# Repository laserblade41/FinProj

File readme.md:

<h1 align="center">FinWatch</h1>

<p align="center">
  An open-source, Zephyr-powered BLE smartwatch with a modular I²C expansion port.<br>
  Final project in Computer Engineering, Bar-Ilan University (Project 323).
</p>

## About

FinWatch is a complete custom smartwatch: the PCB (KiCad), the firmware (Zephyr RTOS / nRF Connect SDK) and a documented protocol for attaching new hardware to it.

Most smartwatches, commercial and open-source, are sealed. The sensors are fixed at manufacture, so a new measurement means a new watch. FinWatch asks whether a finished watch can be extended instead. A four-pin pogo connector on the back of the case carries 3.3 V, GND and an I²C bus. A module clipped onto it describes itself to the watch at runtime, and the firmware does not need to know about that module in advance.

The protocol that makes this work is the **FinWatch Module Protocol (FWMP)**. It is a self-describing, CRC-protected descriptor format. The host treats every byte from a module as untrusted and validates it before use.

The full write-up (design, protocol specification, verification, lessons learned) is in [report/main.pdf](report/main.pdf).

## Features

### Hardware

- **Nordic nRF5340** dual-core SoC (Cortex-M33 application core plus a separate network core running the BLE controller)
- **Nordic nPM1300** PMIC: Li-Po charging, fuel gauge, regulated 1.8 V and 3.3 V rails
- **GC9A01** 240×240 round LCD (SPI) with **CST816S** capacitive touch (I²C)
- **Bosch BMI270** 6-axis IMU with an any-motion interrupt, so the MCU sleeps until the wrist moves
- **Macronix MX25U51245G** 512 Mbit SPI NOR flash for assets and settings
- 32.768 kHz crystal for the RTC
- Two user buttons
- **4-pin pogo expansion port** (3.3 V, GND, SDA, SCL), level-shifted from the SoC's 1.8 V domain by a PCA9306
- 4-layer, 46 mm round PCB designed in KiCad (see [kicad/](kicad/))

### Software

- Zephyr RTOS on the nRF Connect SDK (NCS v3.2.1), with the application running in TF-M non-secure
- LVGL user interface: watch face showing time, date, battery and steps, plus a screen for the attached module
- Interrupt-driven step counting. The IMU wakes the host and the host only samples while the wrist is moving
- BLE with battery level notifications
- LittleFS on the external flash for persistent settings
- **FWMP host**: hot-plug detection, descriptor validation, input and output reports, adaptive polling, and I²C bus recovery
- Expansion runs at the lowest thread priority, so a misbehaving module cannot stall the display, sensors or radio link
- Hardware is described in the Devicetree only, so the same firmware runs on the nRF5340-DK and the custom PCB

## Expansion port and FWMP

FWMP is specified in three layers:

| Layer | What it defines |
| --- | --- |
| Electrical | Four contacts, 3.3 V supply, no pull-ups on the module side, level shifting on the watch |
| Logical | Register map and a TLV descriptor (identity, capabilities, report sizes, preferred poll rate) protected by a CRC-16 |
| Behavioural | Presence detection, enumeration, polling state machine, and recovery from faults |

The host rejects bad magic, bad protocol version, bad CRC, oversized lengths and TLV overruns. It also recovers a jammed bus. All of these paths were exercised with injected faults against a mock module. See section 4 of the report for the full specification and for how to write a compliant module.

## Hardware

| Path | Contents |
| --- | --- |
| [kicad/](kicad/) | Schematic, PCB layout, custom symbols, footprints and 3D models |
| [kicad/watch_thing_alt.pdf](kicad/watch_thing_alt.pdf) | Schematic PDF |
| [kicad/components/board1_nrf5340/](kicad/components/board1_nrf5340/) | Gerber and drill files |

**Revision status**

- **Revision A** was manufactured and assembled. The power rails came up correctly, but `SWDIO` and `SWDCLK` were never routed, so the board could not be programmed.
- **Revision B** exposes SWD on test pads: `SWDIO` on TP4, `SWDCLK` on TP3, `nRESET` on TP2. The lesson from this defect became a pre-fabrication checklist, documented in the report.

## Firmware

Above: the firmware running on the nRF5340-DK with the round display wired up.

```
code/
├── prj.conf                  Kconfig
├── boards/                   Devicetree overlays
├── child_image/hci_ipc.conf  Network-core BLE controller config
└── src/
    ├── main.c
    ├── ble/        BLE and battery notifications
    ├── buttons/    short and long press handling
    ├── display/    LVGL, watch face, module screen
    ├── expansion/  FWMP host, transport and mock module
    ├── pmic/       nPM1300: charger and fuel gauge
    ├── rtc/        timekeeping on the 32.768 kHz crystal
    ├── sensor/     BMI270 any-motion and step counting
    ├── storage/    external flash and LittleFS
    └── touch/      CST816S
```

### Building
```
IMPORTANT: the board itself does not include a bootloader to flash the firmware, in our case we used the one in the nRF5340DK.
```
1. Install the [nRF Connect SDK](https://docs.nordicsemi.com/bundle/ncs-latest/page/nrf/installation.html) **v3.2.1** and open an NCS shell.
2. Build and flash:

```sh
cd code
west build -b nrf5340dk/nrf5340/cpuapp/ns
west flash
```

To test the expansion protocol without any module hardware, enable the mock backend, which simulates a "Test Dial" module:

```sh
west build -b nrf5340dk/nrf5340/cpuapp/ns -- -DCONFIG_FINWATCH_EXPANSION_MOCK=y
```

> For the custom PCB, rename [code/boards/your_board.overlay](code/boards/your_board.overlay) to match your board target and confirm every pin marked `/* [PCB] */` against the schematic before flashing.

## Verification

- Firmware verified on the nRF5340-DK: display, touch, IMU, buttons and BLE
- FWMP verified against a mock module, including hot-plug and six injected-fault classes
- Revision A power rails verified; Revision B bring-up: *TODO*

Full results and their limits are in the report.

## Repository layout

| Folder | Contents |
| --- | --- |
| [code/](code/) | Zephyr firmware |
| [kicad/](kicad/) | PCB design files |
| [report/](report/) | Final project report (LaTeX and PDF) and presentation |
| [pics/](pics/) | Photos and renders |

## Authors

- **Omer Lazaros**
- **Chen Leibov**

Supervised by Prof. Leonid Yavitz. Project mentor: David Freud. Faculty of Engineering, Bar-Ilan University.

## Thanks

Thanks to the Zephyr Project, Nordic Semiconductor (nRF Connect SDK and its courses) and KiCad, whose open tools and documentation made this possible. [ZSWatch](https://github.com/ZSWatch/ZSWatch) was a major inspiration for this project.

## License

*TODO: pick a license (for example GPL-3.0 or MIT for the firmware and CERN-OHL for the hardware) and add a LICENSE file.*

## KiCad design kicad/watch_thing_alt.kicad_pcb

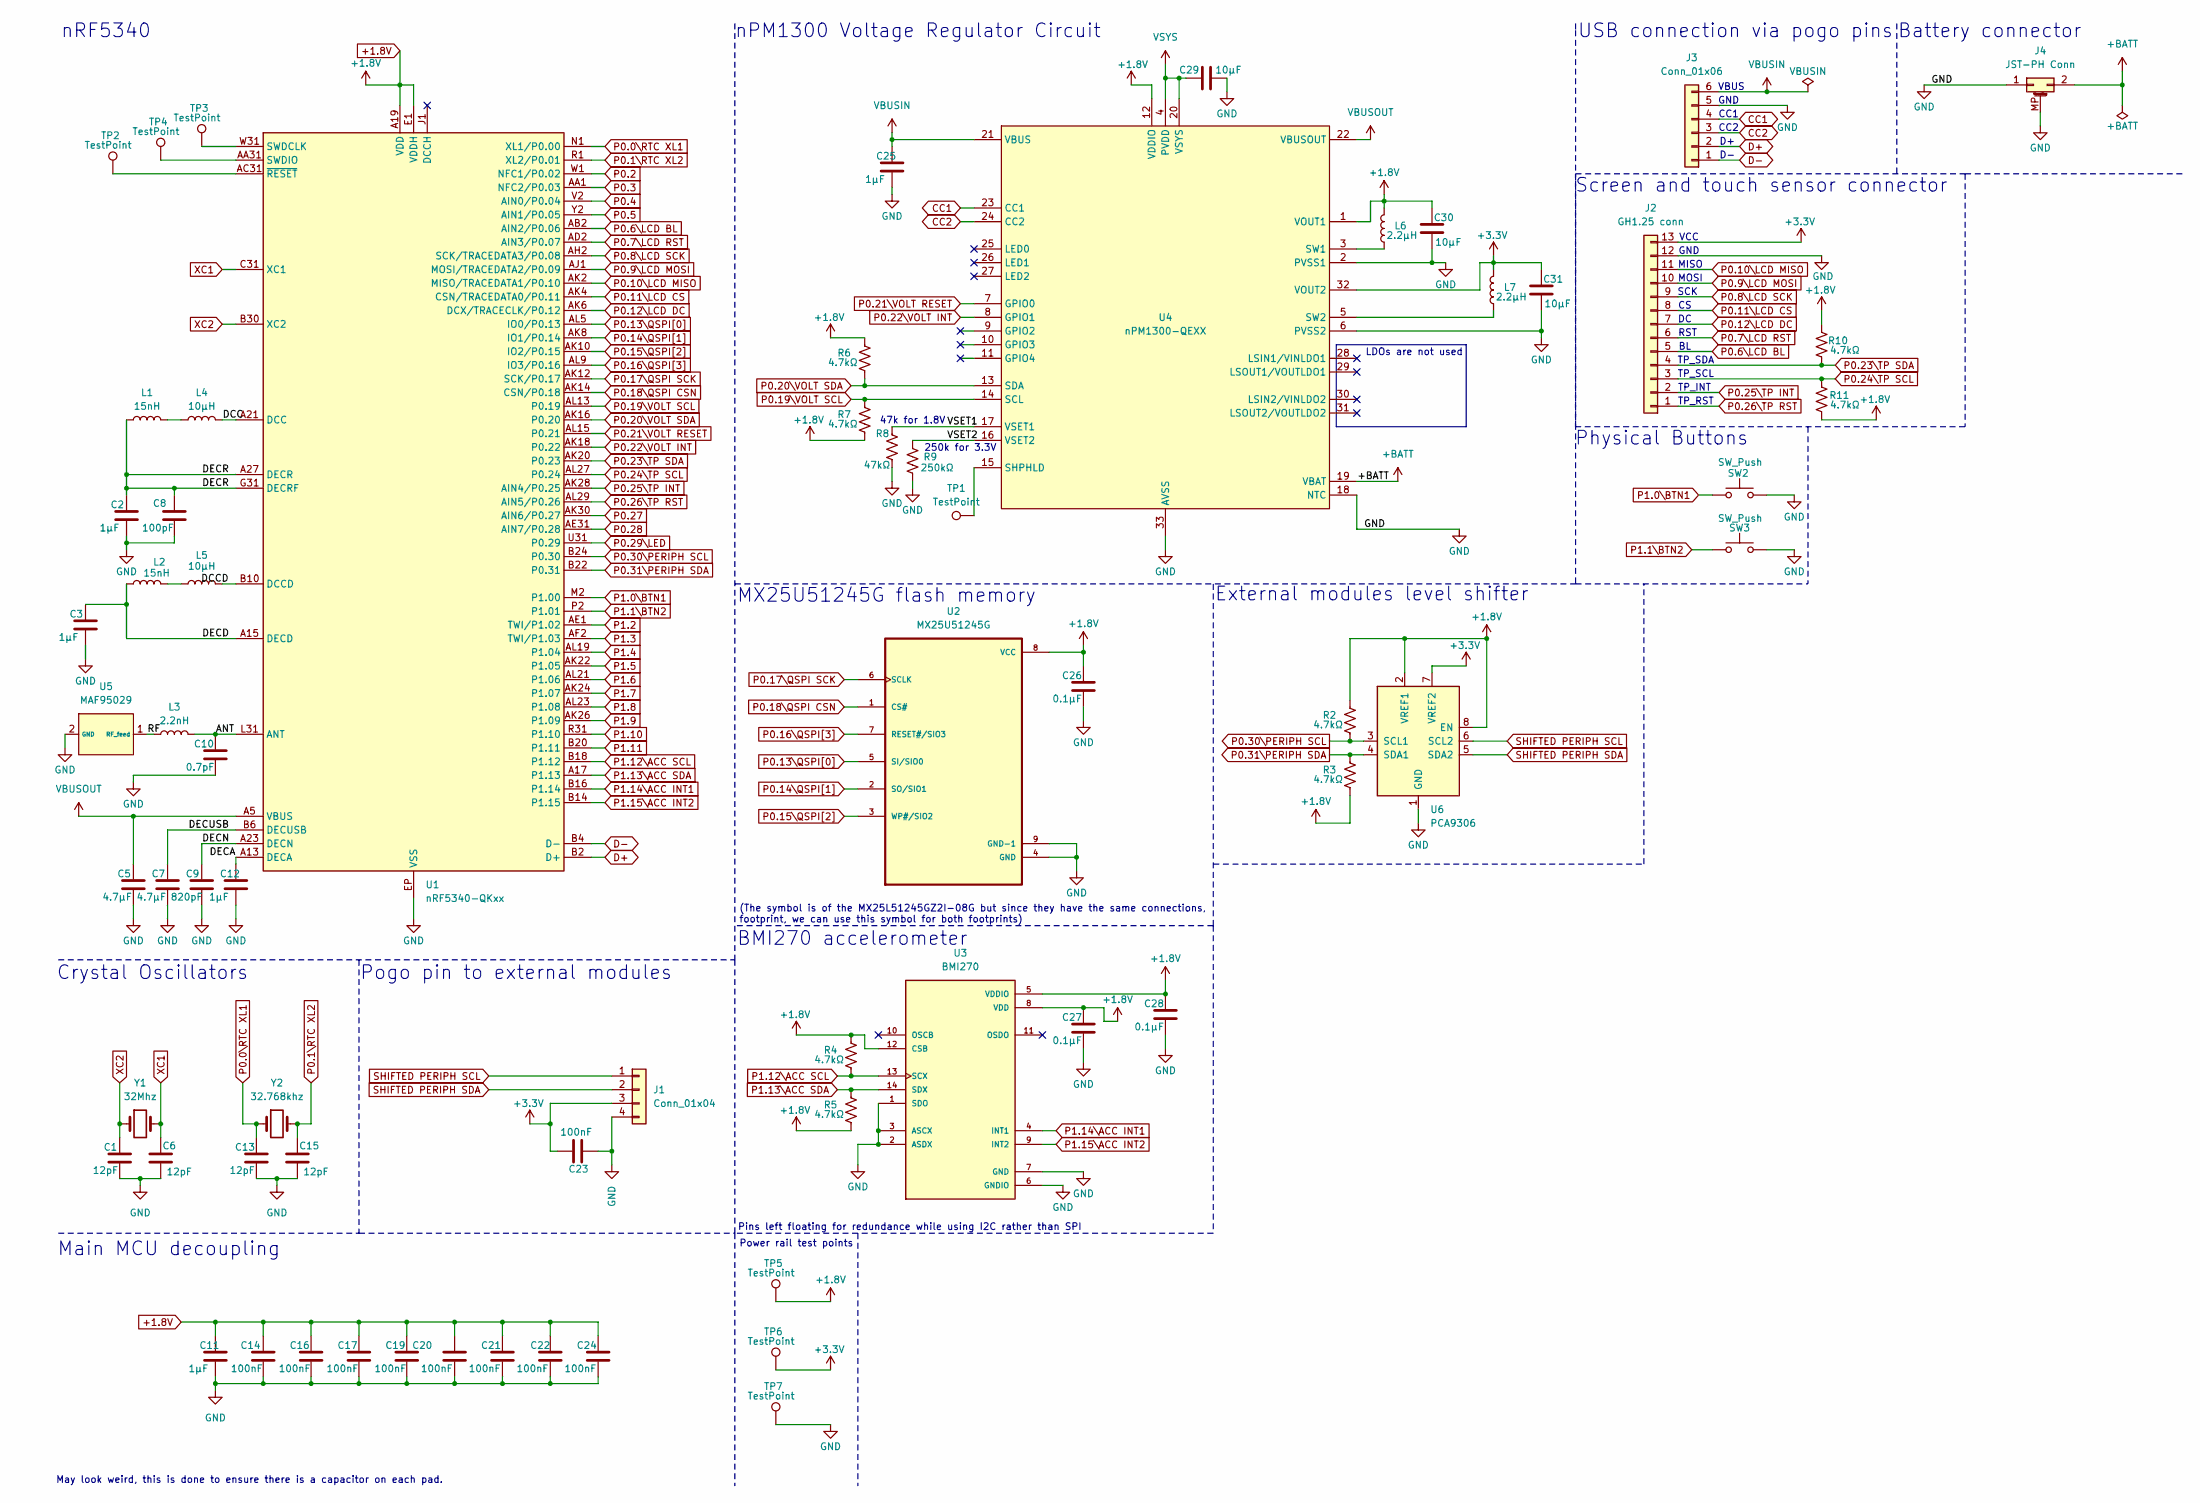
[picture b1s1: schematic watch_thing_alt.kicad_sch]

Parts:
C1, C6, C13, C15: 12pF; C_0402_1005Metric
C2, C3, C11, C12, C25: 1μF; C_0402_1005Metric
C5, C7: 4.7μF; C_0402_1005Metric
C8: 100pF; C_0402_1005Metric
C9: 820pF; C_0402_1005Metric
C10: 0.7pF; C_0402_1005Metric
C14, C16, C17, C19, C20, C21, C22, C23, C24: 100nF; C_0402_1005Metric
C26, C27, C28: 0.1μF; C_0402_1005Metric
C29, C30, C31: 10μF; C_0402_1005Metric
J1: Conn_01x04; 4_Pin_PogoPin
J2: GH1.25 conn; Molex_PicoBlade_53048-1310_1x13_P1.25mm_Horizontal
J3: Conn_01x06; 6_Pin_PogoPin
J4: JST-PH Conn; JST_SH_SM02B-SRSS-TB_1x02-1MP_P1.00mm_Horizontal
L1, L2: 15nH; L_0402_1005Metric
L3: 2.2nH; L_0402_1005Metric
L4, L5: 10μH; L_0402_1005Metric
L6, L7: 2.2μH; L_0402_1005Metric
R2, R3, R4, R5, R6, R7, R10, R11: 4.7kΩ; R_0402_1005Metric
R8: 47kΩ; R_0402_1005Metric
R9: 250kΩ; R_0402_1005Metric
SW2, SW3: SW_Push; SW_Push_1P1T-MP_NO_Horizontal_Alps_SKRTLAE010
TP1, TP2, TP3, TP4, TP5, TP6, TP7: TestPoint; TestPoint_Pad_1.0x1.0mm
U1: nRF5340-QKxx; Nordic_AQFN-94-1EP_7x7mm_P0.4mm
U2: MX25U51245G; SON127P600X800X80-9N
U3: BMI270; XDCR_BMI270
U4: nPM1300-QEXX; QFN-32-1EP_5x5mm_P0.5mm_EP3.6x3.6mm_ThermalVias
U5: MAF95029; MAF92029
U6: PCA9306; SOP50P310X90-8N
Y1: 32Mhz; Crystal_SMD_3225-4Pin_3.2x2.5mm_HandSoldering
Y2: 32.768khz; XTAL_ABS06-32.768KHZ-T

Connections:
+1.8V: C11.1, C14.1, C16.1, C17.1, C19.1, C20.1, C21.1, C22.1, C24.1, C26.1, C27.1, C28.1, C30.1, L6.2, R2.1, R3.2, R4.1, R5.2, R6.1, R7.2, R10.1, R11.2, TP5.1 (1_1), U1.A19 (VDD), U1.AC1 (VDD), U1.AG1 (VDD), U1.AJ31 (VDD), U1.AL3 (VDD), U1.AL7 (VDD), U1.AL11 (VDD), U1.AL17 (VDD), U1.AL25 (VDD), U1.B8 (VDD), U1.B28 (VDD), U1.C1 (VDD), U1.E1 (VDDH), U1.E31 (VDD), U1.L1 (VDD), U1.N31 (VDD), U1.U1 (VDD), U2.8 (VCC), U3.5 (VDDIO), U3.8 (VDD), U3.12 (CSB), U4.1 (VOUT1), U4.12 (VDDIO), U6.2 (VREF1), U6.8 (EN)
+3.3V: C23.2, C31.1, J1.3, J2.13, L7.2, TP6.1 (1_1), U4.32 (VOUT2), U6.7 (VREF2)
+BATT: J4.2, U4.19 (VBAT)
/ANT: C10.1, L3.2, U1.L31 (ANT)
/DCC: L4.2, U1.A21 (DCC)
/DCCD: L5.2, U1.B10 (DCCD)
/DECA: C12.1, U1.A13 (DECA)
/DECD: C3.1, L2.1, U1.A15 (DECD)
/DECN: C9.1, U1.A23 (DECN)
/DECR: C2.1, C8.1, L1.1, U1.A27 (DECR), U1.G31 (DECRF)
/DECUSB: C7.1, U1.B6 (DECUSB)
/RF: L3.1, U5.1 (RF_feed)
/VSET1: R8.2, U4.17 (VSET1)
/VSET2: R9.1, U4.16 (VSET2)
CC1: J3.4, U4.23 (CC1)
CC2: J3.3, U4.24 (CC2)
D+: J3.2, U1.B2 (D+)
D-: J3.1, U1.B4 (D-)
GND: C1.2, C2.2, C3.2, C5.2, C6.2, C7.2, C8.2, C9.2, C10.2, C11.2, C12.2, C13.2, C14.2, C15.2, C16.2, C17.2, C19.2, C20.2, C21.2, C22.2, C23.1, C24.2, C25.2, C26.2, C27.2, C28.2, C29.2, C30.2, C31.2, J1.4, J2.12, J3.5, J4.1, J4.MP (MountPin), R8.1, R9.2, SW2.2, SW3.2, TP7.1 (1_1), U1.EP (VSS), U2.4 (GND), U2.9 (GND-1), U3.1 (SDO), U3.2 (ASDX), U3.3 (ASCX), U3.6 (GNDIO), U3.7 (GND), U4.2 (PVSS1), U4.6 (PVSS2), U4.18 (NTC), U4.33 (AVSS), U5.2 (GND), U6.1 (GND)
unnamed: L1.2, L4.1
unnamed: L2.2, L5.1
unnamed: TP3.1 (1_1), U1.W31 (SWDCLK)
unnamed: TP4.1 (1_1), U1.AA31 (SWDIO)
unnamed: TP2.1 (1_1), U1.AC31 (~RESET)
unnamed: TP1.1 (1_1), U4.15 (SHPHLD)
unnamed: L6.1, U4.3 (SW1)
unnamed: L7.1, U4.5 (SW2)
P0.0\RTC XL1: C13.1, U1.N1 (XL1/P0.00), Y2.1
P0.1\RTC XL2: C15.1, U1.R1 (XL2/P0.01), Y2.2
P0.2: U1.W1 (NFC1/P0.02)
P0.3: U1.AA1 (NFC2/P0.03)
P0.4: U1.V2 (AIN0/P0.04)
P0.5: U1.Y2 (AIN1/P0.05)
P0.6\LCD BL: J2.5, U1.AB2 (AIN2/P0.06)
P0.7\LCD RST: J2.6, U1.AD2 (AIN3/P0.07)
P0.8\LCD SCK: J2.9, U1.AH2 (SCK/TRACEDATA3/P0.08)
P0.9\LCD MOSI: J2.10, U1.AJ1 (MOSI/TRACEDATA2/P0.09)
P0.10\LCD MISO: J2.11, U1.AK2 (MISO/TRACEDATA1/P0.10)
P0.11\LCD CS: J2.8, U1.AK4 (CSN/TRACEDATA0/P0.11)
P0.12\LCD DC: J2.7, U1.AK6 (DCX/TRACECLK/P0.12)
P0.13\QSPI[0]: U1.AL5 (IO0/P0.13), U2.5 (SI/SIO0)
P0.14\QSPI[1]: U1.AK8 (IO1/P0.14), U2.2 (SO/SIO1)
P0.15\QSPI[2]: U1.AK10 (IO2/P0.15), U2.3 (WP#/SIO2)
P0.16\QSPI[3]: U1.AL9 (IO3/P0.16), U2.7 (RESET#/SIO3)
P0.17\QSPI SCK: U1.AK12 (SCK/P0.17), U2.6 (SCLK)
P0.18\QSPI CSN: U1.AK14 (CSN/P0.18), U2.1 (CS#)
P0.19\VOLT SCL: R7.1, U1.AL13 (P0.19), U4.14 (SCL)
P0.20\VOLT SDA: R6.2, U1.AK16 (P0.20), U4.13 (SDA)
P0.21\VOLT RESET: U1.AL15 (P0.21), U4.7 (GPIO0)
P0.22\VOLT INT: U1.AK18 (P0.22), U4.8 (GPIO1)
P0.23\TP SDA: J2.4, R10.2, U1.AK20 (P0.23)
P0.24\TP SCL: J2.3, R11.1, U1.AL27 (P0.24)
P0.25\TP INT: J2.2, U1.AK28 (AIN4/P0.25)
P0.26\TP RST: J2.1, U1.AL29 (AIN5/P0.26)
P0.27: U1.AK30 (AIN6/P0.27)
P0.28: U1.AE31 (AIN7/P0.28)
P0.29\LED: U1.U31 (P0.29)
P0.30\PERIPH SCL: R2.2, U1.B24 (P0.30), U6.3 (SCL1)
P0.31\PERIPH SDA: R3.1, U1.B22 (P0.31), U6.4 (SDA1)
P1.0\BTN1: SW2.1, U1.M2 (P1.00)
P1.1\BTN2: SW3.1, U1.P2 (P1.01)
P1.2: U1.AE1 (TWI/P1.02)
P1.3: U1.AF2 (TWI/P1.03)
P1.4: U1.AL19 (P1.04)
P1.5: U1.AK22 (P1.05)
P1.6: U1.AL21 (P1.06)
P1.7: U1.AK24 (P1.07)
P1.8: U1.AL23 (P1.08)
P1.9: U1.AK26 (P1.09)
P1.10: U1.R31 (P1.10)
P1.11: U1.B20 (P1.11)
P1.12\ACC SCL: R4.2, U1.B18 (P1.12), U3.13 (SCX)
P1.13\ACC SDA: R5.1, U1.A17 (P1.13), U3.14 (SDX)
P1.14\ACC INT1: U1.B16 (P1.14), U3.4 (INT1)
P1.15\ACC INT2: U1.B14 (P1.15), U3.9 (INT2)
SHIFTED PERIPH SCL: J1.1, U6.6 (SCL2)
SHIFTED PERIPH SDA: J1.2, U6.5 (SDA2)
VBUSIN: C25.1, J3.6, U4.21 (VBUS)
VBUSOUT: C5.1, U1.A5 (VBUS), U4.22 (VBUSOUT)
VSYS: C29.1, U4.4 (PVDD), U4.20 (VSYS)
XC1: C6.1, U1.C31 (XC1), Y1.2
XC2: C1.1, U1.B30 (XC2), Y1.1

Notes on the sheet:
BMI270 accelerometer
Physical Buttons
TP_SCL
GND
LDOs are not used
Pogo pin to external modules
250k for 3.3V
47k for 1.8V
nPM1300 Voltage Regulator Circuit
MX25U51245G flash memory
VCC
Crystal Oscillators
CC2
External modules level shifter
MISO
USB connection via pogo pins
MOSI
May look weird, this is done to ensure there is a capacitor on each pad.
nRF5340
RST
TP_SDA
Pins left floating for redundance while using I2C rather than SPI
TP_RST
(The symbol is of the MX25L51245GZ2I-08G but since they have the same connections, footprint, we can use this symbol for both footprints)
Screen and touch sensor connector
TP_INT
VBUS
SCK
Main MCU decoupling
GND
Power rail test points
CC1
Battery connector

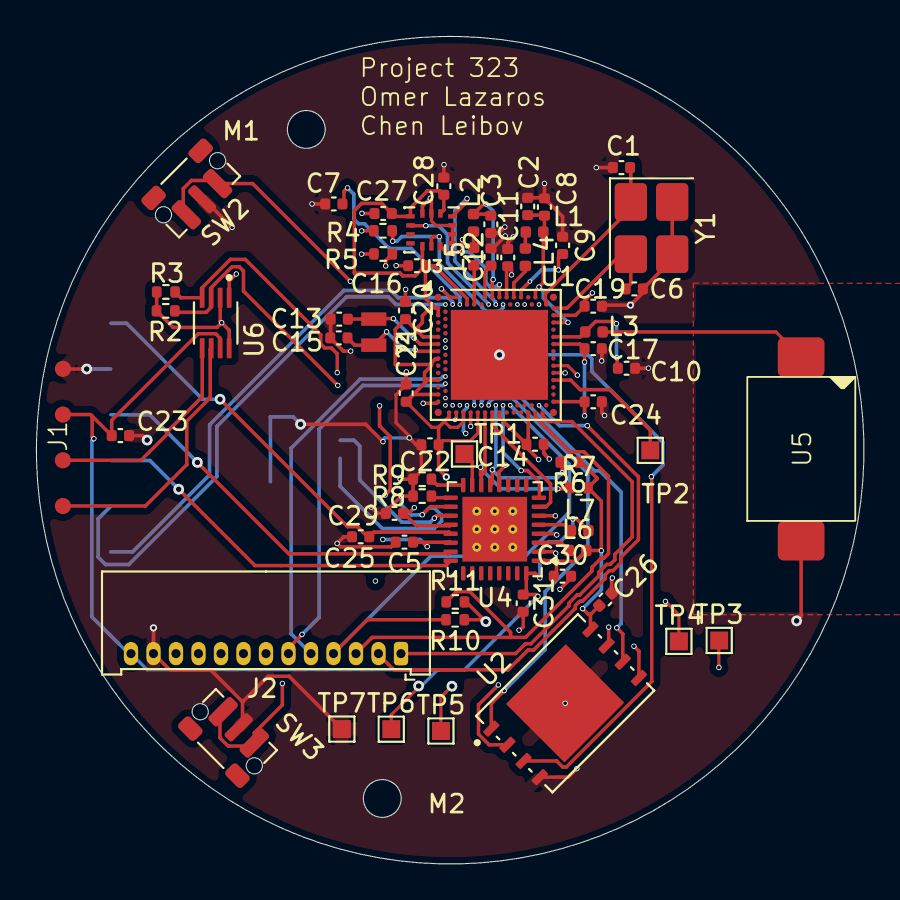
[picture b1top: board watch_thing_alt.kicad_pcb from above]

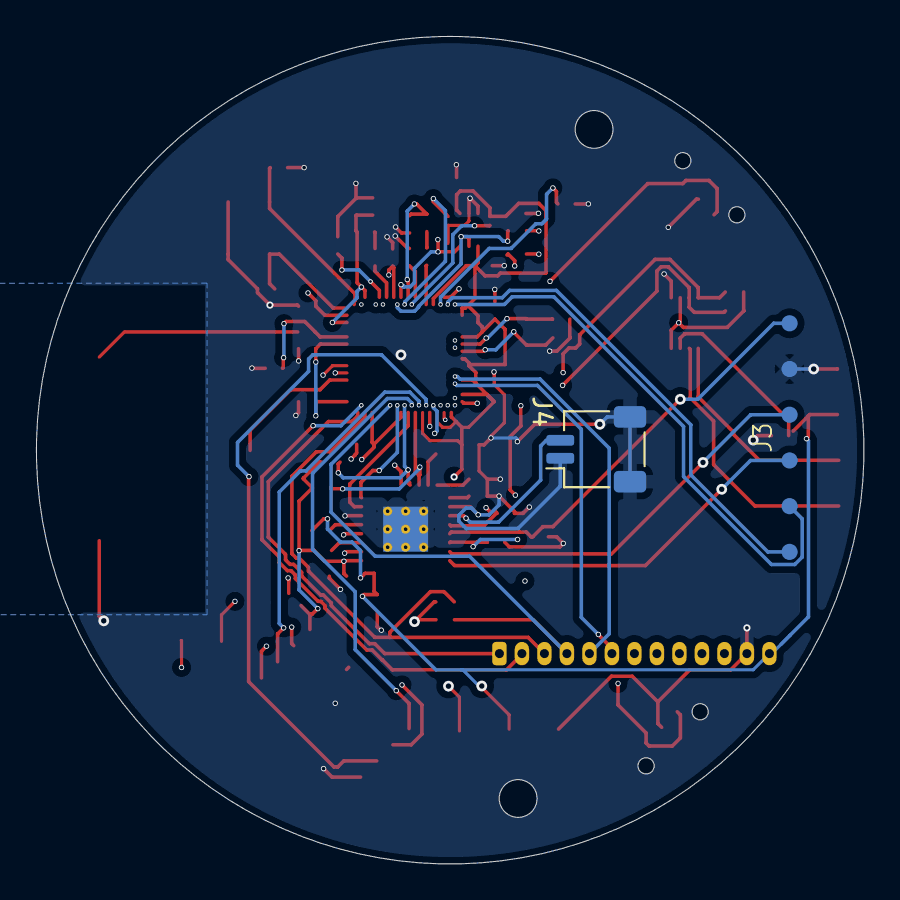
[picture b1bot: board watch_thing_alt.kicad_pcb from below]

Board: 4 copper layers, 46.0 x 46.0 mm, 69 parts (2 on the bottom side), 65 nets.

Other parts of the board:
M1, M2: MountingHole_2.1mm
